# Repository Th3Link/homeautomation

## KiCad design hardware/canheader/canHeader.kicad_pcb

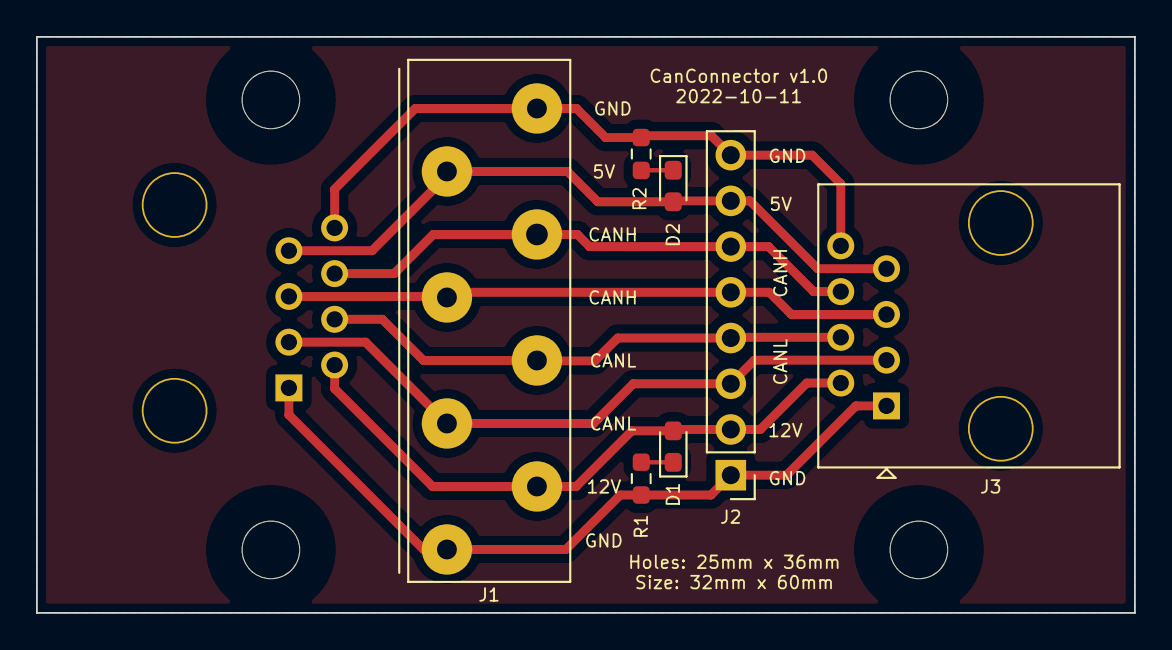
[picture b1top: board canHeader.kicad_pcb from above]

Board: 2 copper layers, 61.0 x 32.0 mm, 12 parts (1 on the bottom side), 10 nets.

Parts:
D1, D2: LED; LED_0603_1608Metric_Pad1.05x0.95mm_HandSolder
H1, H2, H3, H4: MountingHole; MountingHole_3.2mm_M3_DIN965
J1: WAGO250-208
J2: Conn_01x08_Male; PinHeader_1x08_P2.54mm_Vertical
J3, J4: RJ45-CAN; RJ45_OST_PJ012-8P8CX_Vertical
R1, R2: R; R_0603_1608Metric_Pad0.98x0.95mm_HandSolder

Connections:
+5V: D2.2, J1.7, J2.7, J3.7, J4.7
+12V: D1.2, J1.2, J2.2, J3.2, J4.2
/CANH+: J1.6, J2.6, J3.6, J4.6
/CANH-: J1.5, J2.5, J3.5, J4.5
/CANL+: J1.3, J2.3, J3.3, J4.3
/CANL-: J1.4, J2.4, J3.4, J4.4
/GND5V: J1.8, J2.8, J3.8, J4.8, R2.2
/GND12V: J1.1, J2.1, J3.1, J4.1, R1.1
unnamed: D1.1, R1.2
unnamed: D2.1, R2.1

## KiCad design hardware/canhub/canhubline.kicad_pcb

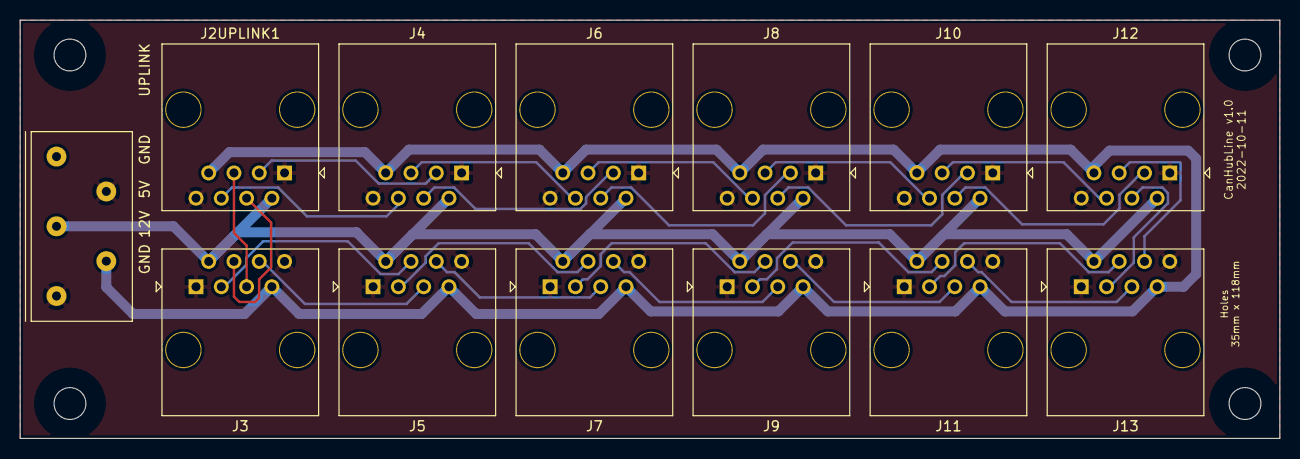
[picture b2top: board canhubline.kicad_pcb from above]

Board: 2 copper layers, 126.5 x 42.0 mm, 17 parts (0 on the bottom side), 27 nets.

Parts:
H1, H2, H3, H4: MountingHole; MountingHole_3.2mm_M3
J1: WAGO 250-205; WAGO250-205
J2UPLINK1, J3, J4, J5, J6, J7, J8, J9, J10, J11, J12, J13: RJ45-CAN; RJ45_OST_PJ012-8P8CX_Vertical

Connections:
+5V: J1.2, J2UPLINK1.7 (+5V), J3.7 (+5V), J4.7 (+5V), J5.7 (+5V), J6.7 (+5V), J7.7 (+5V), J8.7 (+5V), J9.7 (+5V), J10.7 (+5V), J11.7 (+5V), J12.7 (+5V), J13.7 (+5V)
+12V: J1.3, J2UPLINK1.2 (+12V), J3.2 (+12V), J4.2 (+12V), J5.2 (+12V), J6.2 (+12V), J7.2 (+12V), J8.2 (+12V), J9.2 (+12V), J10.2 (+12V), J11.2 (+12V), J12.2 (+12V), J13.2 (+12V)
GND: J1.1, J1.4, J2UPLINK1.1 (GND), J2UPLINK1.8 (GND), J3.1 (GND), J3.8 (GND), J4.1 (GND), J4.8 (GND), J5.1 (GND), J5.8 (GND), J6.1 (GND), J6.8 (GND), J7.1 (GND), J7.8 (GND), J8.1 (GND), J8.8 (GND), J9.1 (GND), J9.8 (GND), J10.1 (GND), J10.8 (GND), J11.1 (GND), J11.8 (GND), J12.1 (GND), J12.8 (GND), J13.1 (GND), J13.8 (GND)
unnamed: J2UPLINK1.3 (CANL), J4.3 (CANL)
unnamed: J2UPLINK1.4 (CANL), J3.4 (CANL)
unnamed: J2UPLINK1.5 (CANH), J3.5 (CANH)
unnamed: J2UPLINK1.6 (CANH), J4.6 (CANH)
unnamed: J3.3 (CANL), J5.4 (CANL)
unnamed: J3.6 (CANH), J5.5 (CANH)
unnamed: J4.4 (CANL), J6.3 (CANL)
unnamed: J4.5 (CANH), J6.6 (CANH)
unnamed: J5.3 (CANL), J7.4 (CANL)
unnamed: J5.6 (CANH), J7.5 (CANH)
unnamed: J6.4 (CANL), J8.3 (CANL)
unnamed: J6.5 (CANH), J8.6 (CANH)
unnamed: J7.3 (CANL), J9.4 (CANL)
unnamed: J7.6 (CANH), J9.5 (CANH)
unnamed: J8.4 (CANL), J10.3 (CANL)
unnamed: J10.4 (CANL), J12.3 (CANL)
unnamed: J10.5 (CANH), J12.6 (CANH)
unnamed: J8.5 (CANH), J10.6 (CANH)
unnamed: J11.3 (CANL), J13.4 (CANL)
unnamed: J9.3 (CANL), J11.4 (CANL)
unnamed: J9.6 (CANH), J11.5 (CANH)
unnamed: J11.6 (CANH), J13.5 (CANH)
unnamed: J12.4 (CANL), J13.3 (CANL)
unnamed: J12.5 (CANH), J13.6 (CANH)
